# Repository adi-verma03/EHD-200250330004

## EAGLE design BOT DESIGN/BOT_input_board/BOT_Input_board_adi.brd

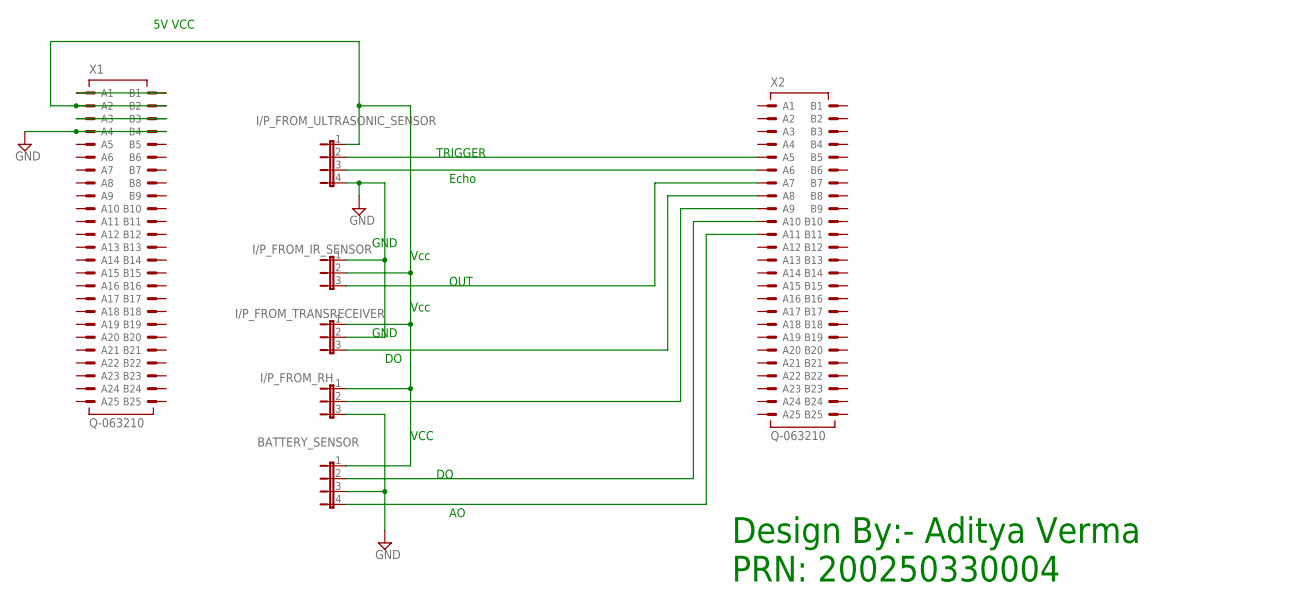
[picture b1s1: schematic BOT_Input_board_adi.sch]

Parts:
BATTERY_SENSOR: JP4E; JP4
I/P_FROM_IR_SENSOR: JP2E; JP2
I/P_FROM_RH: JP2E; JP2
I/P_FROM_TRANSRECEIVER: JP2E; JP2
I/P_FROM_ULTRASONIC_SENSOR: JP4E; JP4
X1, X2: Q-063210; 063210

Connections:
GND: BATTERY_SENSOR.3, I/P_FROM_IR_SENSOR.1, I/P_FROM_RH.3, I/P_FROM_TRANSRECEIVER.2, I/P_FROM_ULTRASONIC_SENSOR.4, X1.A4, X1.B4
unnamed: I/P_FROM_ULTRASONIC_SENSOR.3, X2.A6
unnamed: X1.A1, X1.B1
unnamed: BATTERY_SENSOR.1, I/P_FROM_IR_SENSOR.2, I/P_FROM_RH.1, I/P_FROM_TRANSRECEIVER.1, I/P_FROM_ULTRASONIC_SENSOR.1, X1.A2, X1.B2
unnamed: X1.A3, X1.B3
unnamed: I/P_FROM_ULTRASONIC_SENSOR.2, X2.A5
unnamed: I/P_FROM_IR_SENSOR.3, X2.A7
unnamed: I/P_FROM_TRANSRECEIVER.3, X2.A8
unnamed: I/P_FROM_RH.2, X2.A9
unnamed: BATTERY_SENSOR.2, X2.A10
unnamed: BATTERY_SENSOR.4, X2.A11

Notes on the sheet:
5V VCC
Vcc
GND
TRIGGER
Echo
OUT
VCC
Design By:- Aditya Verma PRN: 200250330004

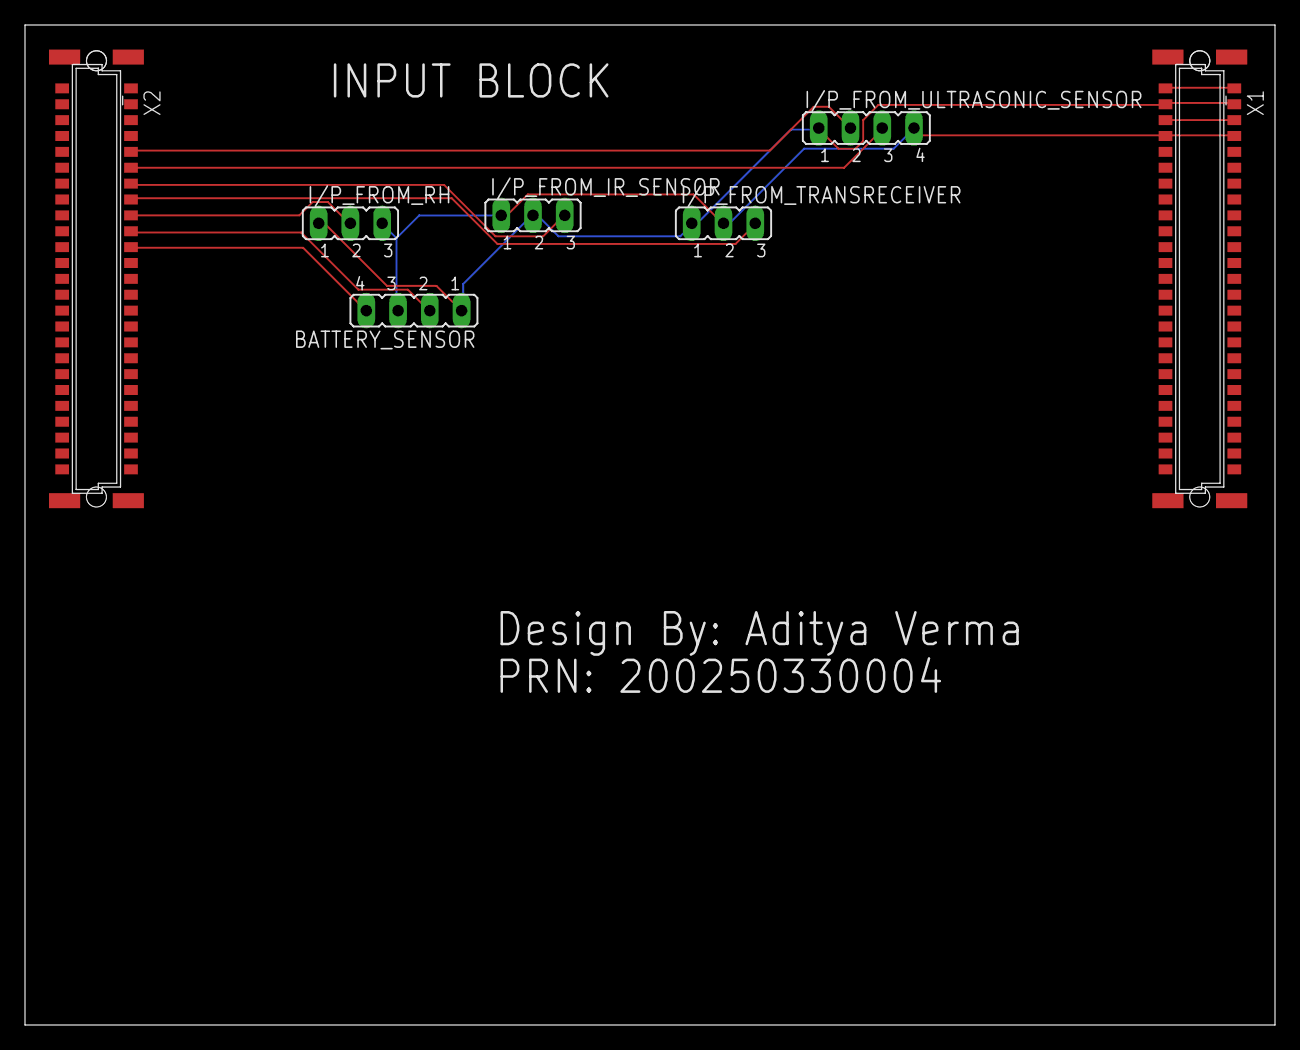
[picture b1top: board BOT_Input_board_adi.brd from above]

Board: 2 copper layers, 100.0 x 80.0 mm, 7 parts (0 on the bottom side), 11 nets.

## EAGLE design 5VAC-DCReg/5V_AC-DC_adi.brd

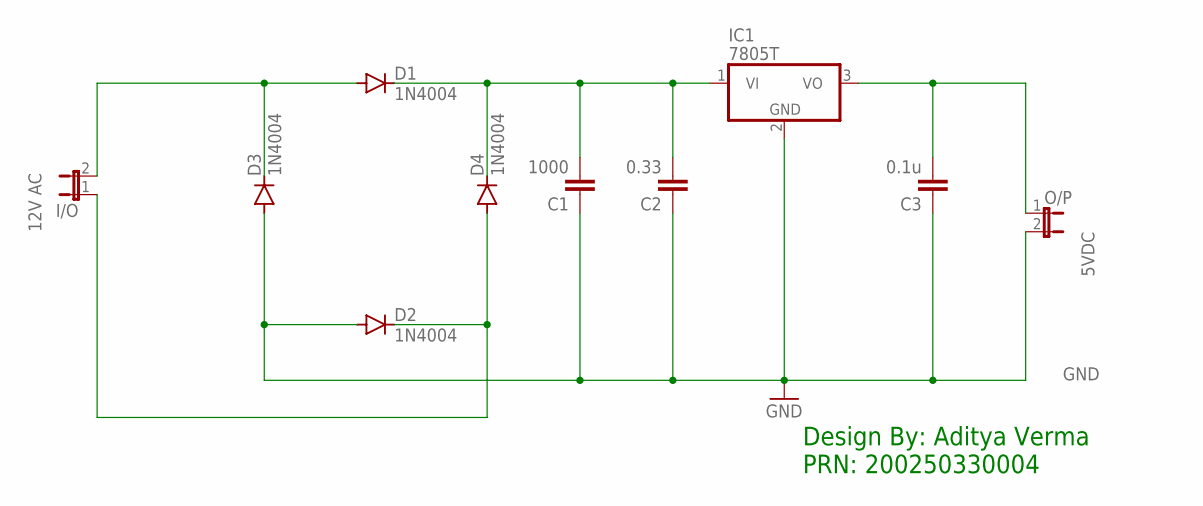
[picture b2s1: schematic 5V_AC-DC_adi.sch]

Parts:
C1: 1000; C2.5-3
C2: 0.33; C2.5-3
C3: 0.1u; C2.5-3
D1, D2, D3, D4: 1N4004; DO41-10
I/O: JP1E; JP1
IC1: 7805T; TO220H
O/P: JP1E; JP1

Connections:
GND: C1.1, C2.1, C3.1, D2.A, D3.A, IC1.2 (GND), O/P.2
unnamed: D1.A, D3.C, I/O.2
unnamed: D2.C, D4.A, I/O.1
unnamed: C1.2, C2.2, D1.C, D4.C, IC1.1 (VI)
unnamed: C3.2, IC1.3 (VO), O/P.1

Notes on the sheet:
Design By: Aditya Verma PRN: 200250330004

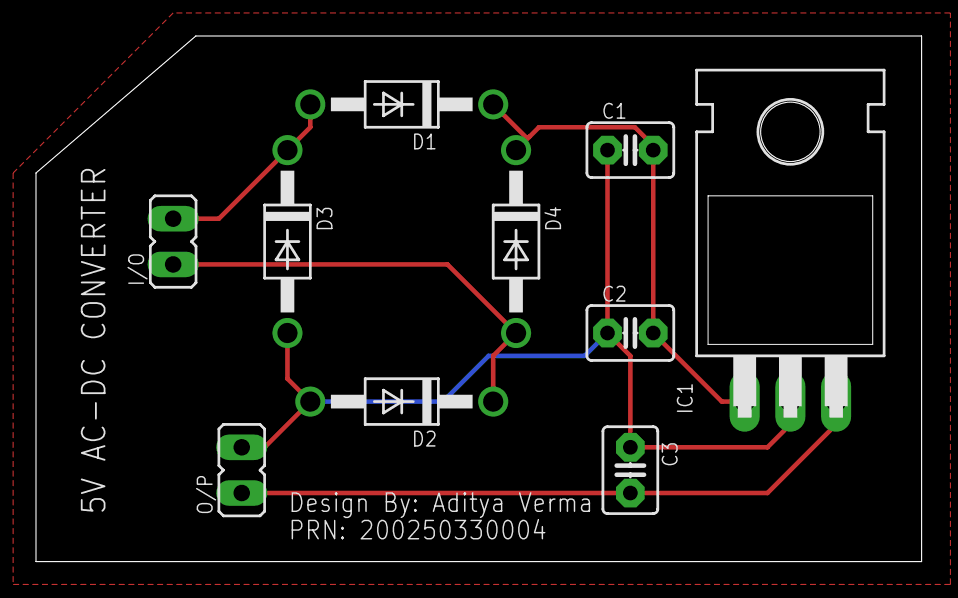
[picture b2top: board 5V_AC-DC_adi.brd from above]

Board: 2 copper layers, 49.2 x 29.2 mm, 10 parts (0 on the bottom side), 5 nets.

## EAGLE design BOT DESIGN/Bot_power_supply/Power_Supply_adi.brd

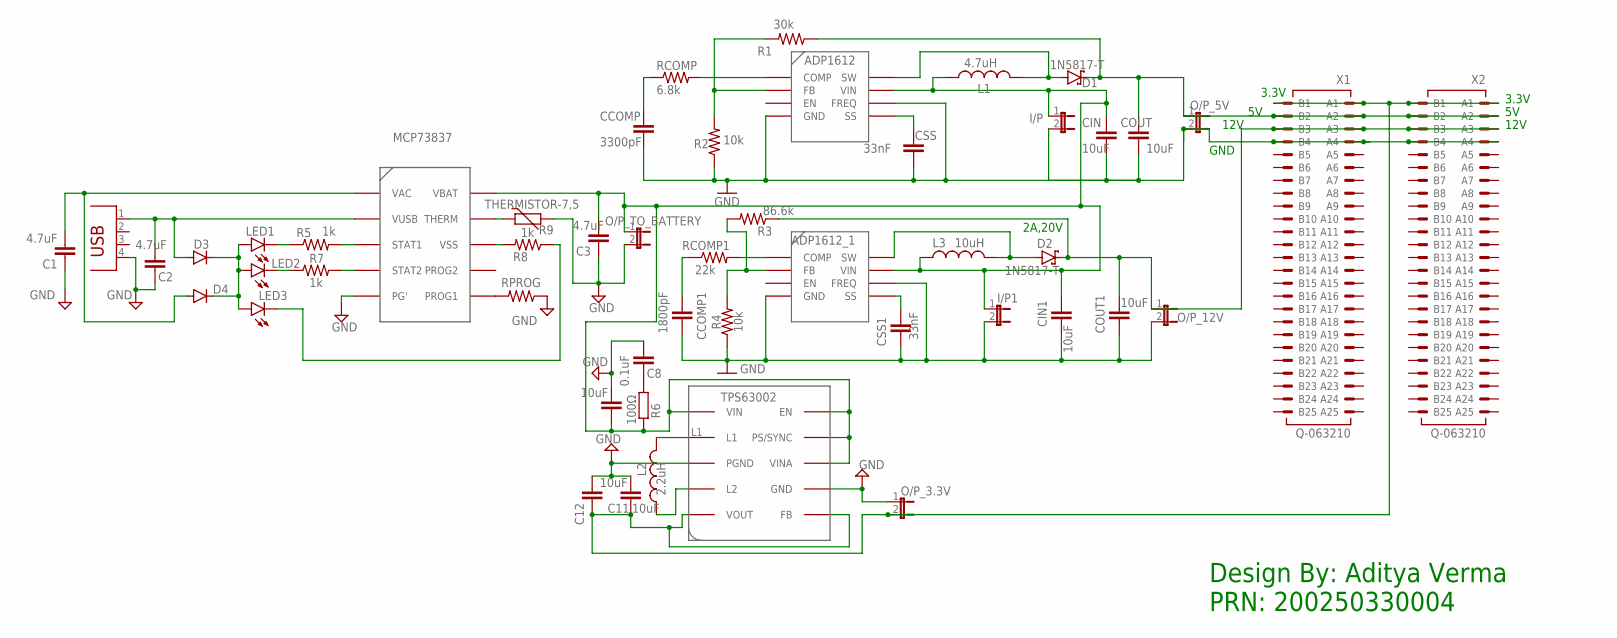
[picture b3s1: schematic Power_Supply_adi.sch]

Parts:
ADP1612, ADP1612_1: ADP1612_DEV; ADP1612_FOOT
C1, C2, C3: 4.7uF; C2.5-3
C8: 0.1uF; C2.5-2
C10, C11, C12: 10uF; C2.5-2
CCOMP: 3300pF; C2.5-3
CCOMP1: 1800pF; C2.5-3
CIN, CIN1: 10uF; C2.5-3
COUT, COUT1: 10uF; C2.5-3
CSS, CSS1: 33nF; C2.5-3
D1, D2: 1N5817-T; DO41-7.6
D3, D4: 1N4004; DO41-10
I/P, I/P1: JP1E; JP1
L1: 4.7uH; 0204/7
L2: 2.2uH; 0207/7
L3: 10uH; 0204/7
LED1, LED3: LED3MM
LED2: LEDLD260; LD260
MCP73837: MCP73837-DEV; MCP73837
O/P_3.3V, O/P_5V, O/P_12V: JP1E; JP1
O/P_TO_BATTERY: JP1E; JP1
R1: 30k; 0204V
R2, R4: 10k; 0204V
R3: 86.6k; 0204V
R5, R7, R8: 1k; 0204V
R6: 100Ω; 0207/10
R9: THERMISTOR-7,5; R-7,5
RCOMP: 6.8k; 0204V
RCOMP1: 22k; 0204V
RPROG: R-US_0204/2V; 0204V
TPS63002: TPS63002
USB: PN61729
X1, X2: Q-063210; 063210

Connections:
GND: ADP1612.FREQ, ADP1612.GND, ADP1612_1.FREQ, ADP1612_1.GND, C1.1, C2.1, C3.1, C8.2, C10.2, C11.2, C12.2, CCOMP.2, CCOMP1.2, CIN.2, CIN1.2, COUT.2, COUT1.2, CSS.2, CSS1.2, I/P.2, I/P1.2, MCP73837.PG', O/P_3.3V.1, O/P_5V.2, O/P_12V.2, O/P_TO_BATTERY.2, R2.1, R4.1, R9.2, RPROG.1, TPS63002.GND, TPS63002.PGND, USB.4, X1.A4, X1.B4, X2.A4, X2.B4
unnamed: ADP1612.COMP, RCOMP.2
unnamed: CCOMP.1, RCOMP.1
unnamed: COUT.1, D1.C, O/P_5V.1, R1.1, X1.A2, X1.B2, X2.A2, X2.B2
unnamed: ADP1612.FB, R1.2, R2.2
unnamed: L2.1, TPS63002.L1
unnamed: ADP1612.SS, CSS.1
unnamed: ADP1612.SW, D1.A, L1.2
unnamed: ADP1612_1.COMP, RCOMP1.2
unnamed: CCOMP1.1, RCOMP1.1
unnamed: COUT1.1, D2.C, O/P_12V.1, R3.1, X1.A3, X1.B3, X2.A3, X2.B3
unnamed: L2.2, TPS63002.L2
unnamed: ADP1612_1.FB, R3.2, R4.2
unnamed: ADP1612_1.SS, CSS1.1
unnamed: MCP73837.VSS, R8.2
unnamed: ADP1612_1.SW, D2.A, L3.2
unnamed: MCP73837.STAT1, R5.2
unnamed: MCP73837.STAT2, R7.2
unnamed: ADP1612.VIN, ADP1612_1.VIN, C3.2, C10.1, CIN.1, CIN1.1, I/P.1, I/P1.1, L1.1, L3.1, MCP73837.VBAT, O/P_TO_BATTERY.1, R6.1, TPS63002.EN, TPS63002.PS/SYNC, TPS63002.VIN, TPS63002.VINA
unnamed: C8.1, R6.2
unnamed: MCP73837.PROG1, RPROG.2
unnamed: MCP73837.THERM, R9.1
unnamed: C2.2, D3.A, MCP73837.VUSB, USB.1
unnamed: LED1.K (C), R5.1
unnamed: LED2.K (C), R7.1
unnamed: D3.C, D4.C, LED1.A, LED2.A, LED3.A
unnamed: C1.2, D4.A, MCP73837.VAC
unnamed: LED3.K (C), R8.1
unnamed: C11.1, C12.1, O/P_3.3V.2, TPS63002.FB, TPS63002.VOUT, X1.A1, X1.B1, X2.A1, X2.B1

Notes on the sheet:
2A,20V
3.3V
12V
GND
Design By: Aditya Verma PRN: 200250330004

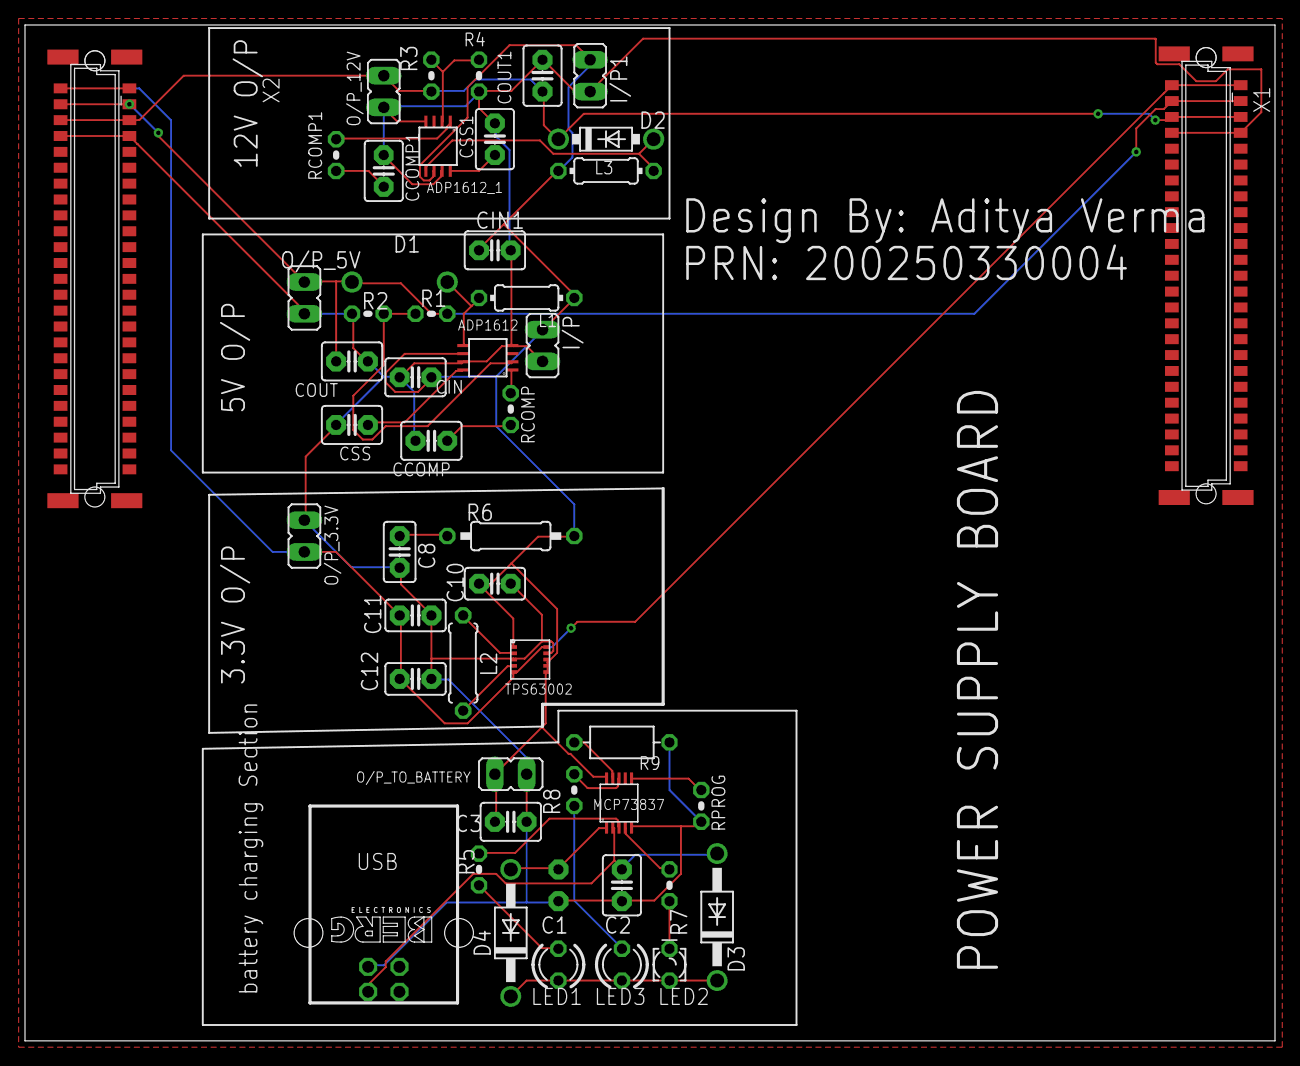
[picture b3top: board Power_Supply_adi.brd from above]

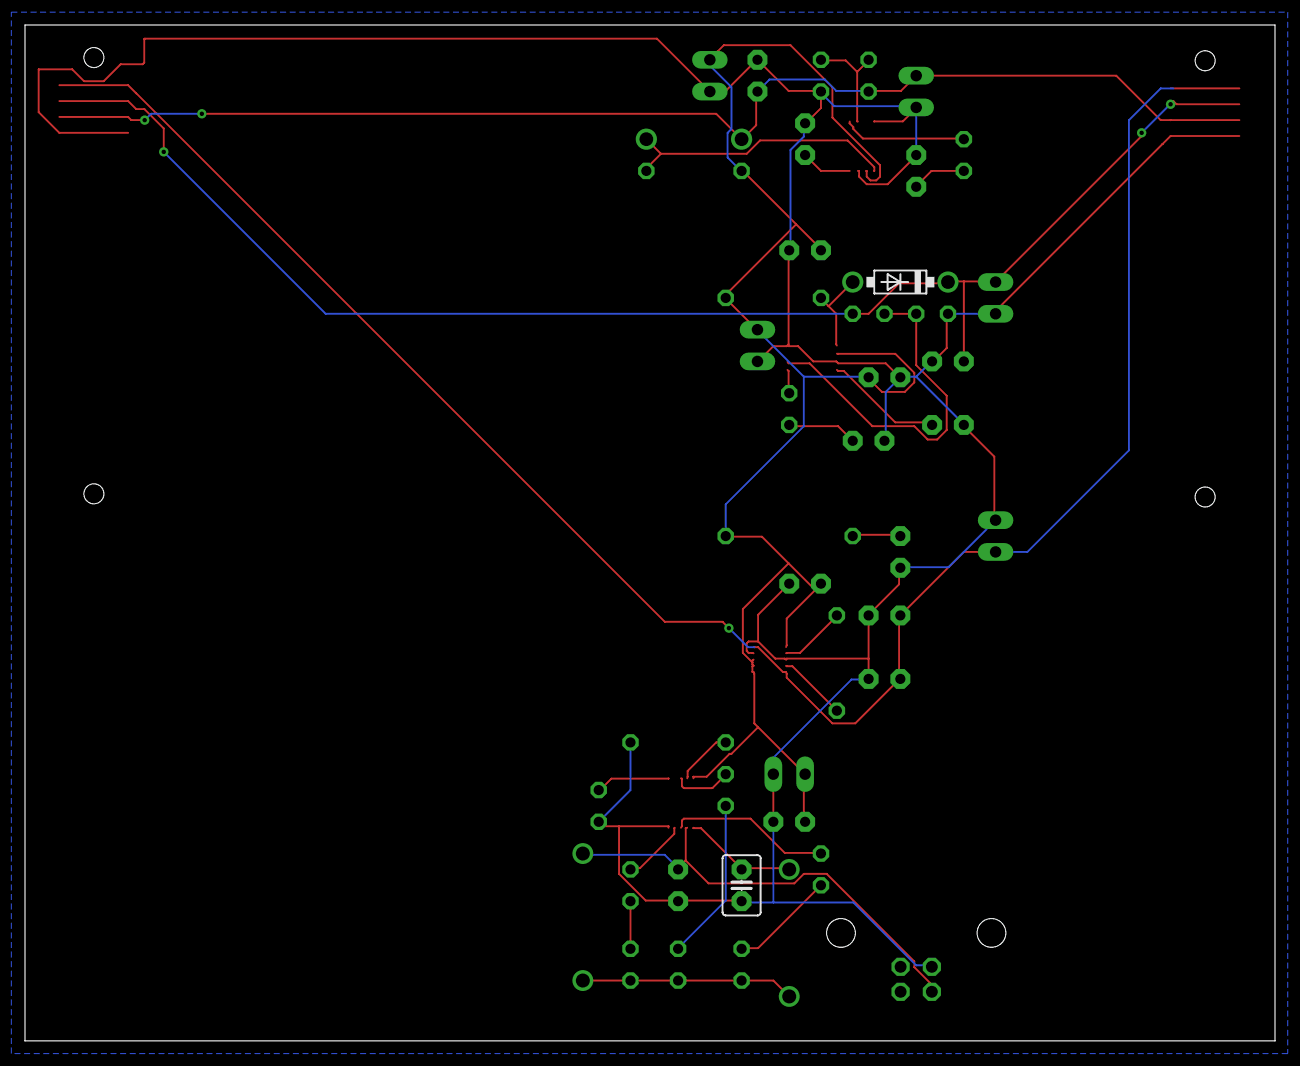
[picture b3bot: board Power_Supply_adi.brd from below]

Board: 2 copper layers, 100.0 x 81.3 mm, 50 parts (2 on the bottom side), 29 nets.

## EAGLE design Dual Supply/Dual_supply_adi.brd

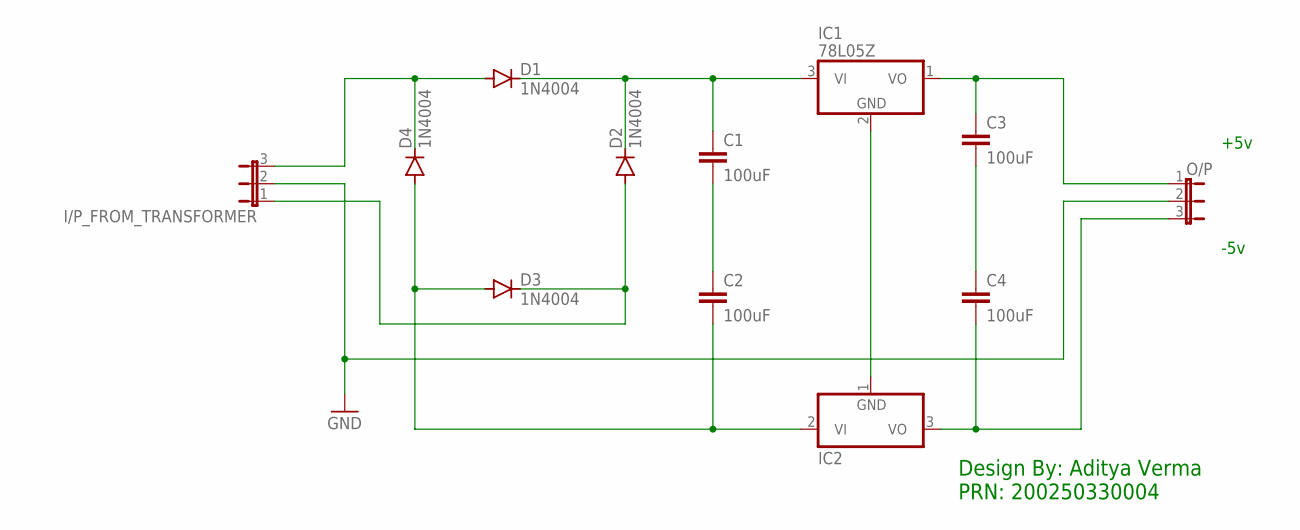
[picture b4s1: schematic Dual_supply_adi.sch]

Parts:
C1, C2, C3, C4: 100uF; C2.5-3
D1, D2, D3, D4: 1N4004; DO41-10
I/P_FROM_TRANSFORMER: JP2E; JP2
IC1: 78L05Z; TO92
IC2: 79L05Z; TO92
O/P: JP2E; JP2

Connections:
GND: I/P_FROM_TRANSFORMER.2, O/P.2
unnamed: C2.2, D3.A, D4.A, IC2.2 (VI)
unnamed: IC1.2 (GND), IC2.1 (GND)
unnamed: C4.2, IC2.3 (VO), O/P.3
unnamed: D1.A, D4.C, I/P_FROM_TRANSFORMER.3
unnamed: C1.1, D1.C, D2.C, IC1.3 (VI)
unnamed: D2.A, D3.C, I/P_FROM_TRANSFORMER.1
unnamed: C3.2, C4.1
unnamed: C1.2, C2.1
unnamed: C3.1, IC1.1 (VO), O/P.1

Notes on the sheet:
+5v
-5v
Design By: Aditya Verma PRN: 200250330004

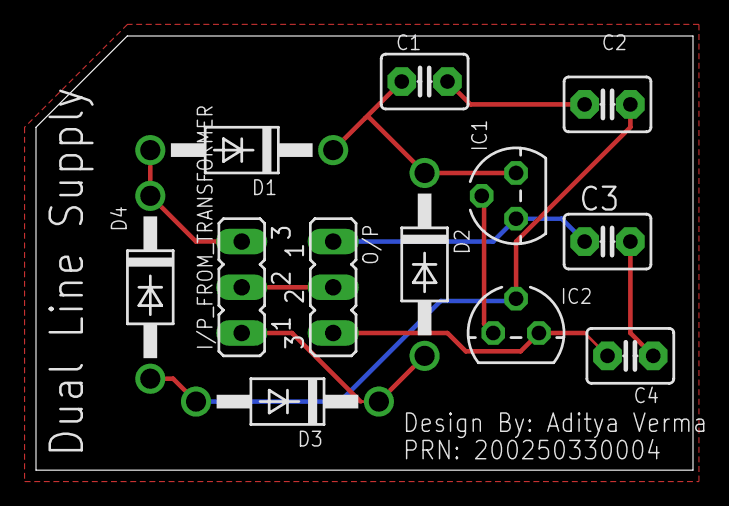
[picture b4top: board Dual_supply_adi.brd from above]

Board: 2 copper layers, 36.5 x 24.1 mm, 12 parts (0 on the bottom side), 10 nets.

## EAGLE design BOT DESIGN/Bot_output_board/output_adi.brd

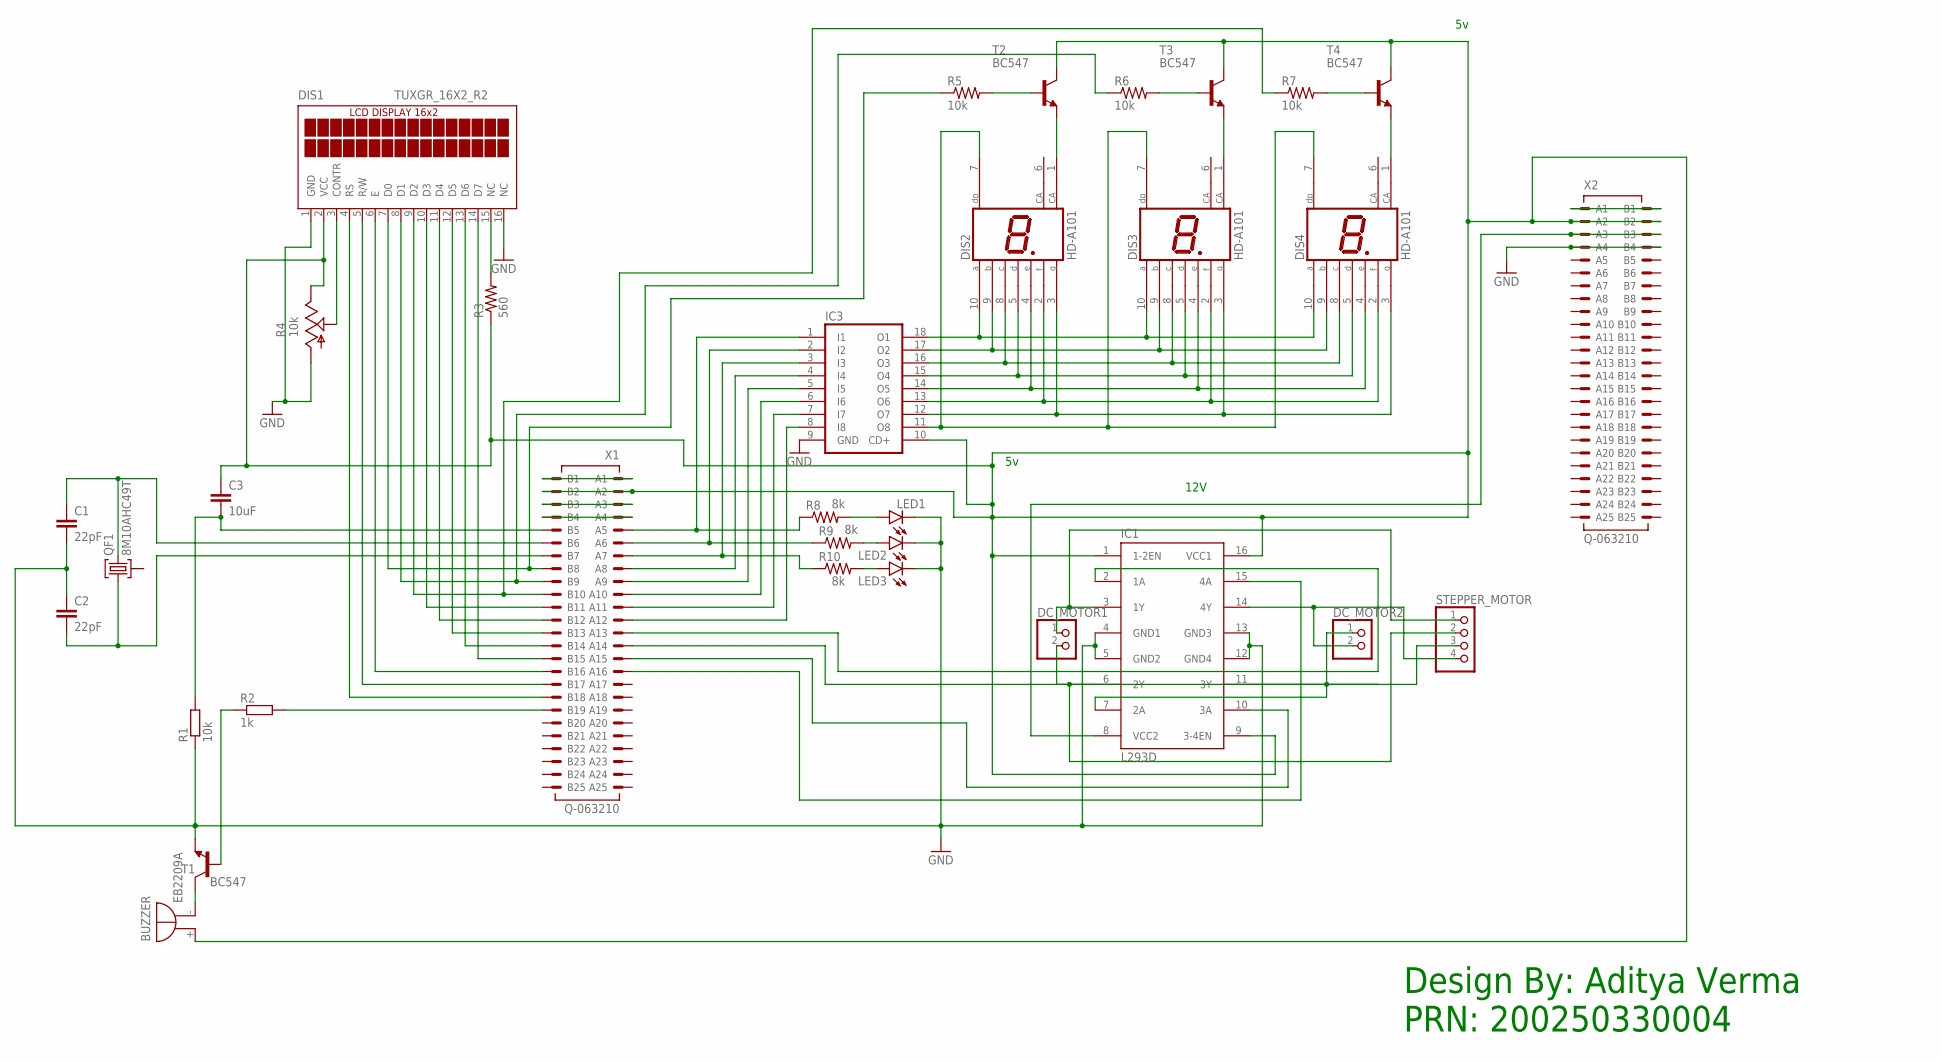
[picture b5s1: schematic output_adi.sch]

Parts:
BUZZER: EB2209A
C1, C2: 22pF; C2.5-3
C3: 10uF; C2.5-3
DC_MOTOR1, DC_MOTOR2: PINHD-1X2; 1X02
DIS1: TUXGR_16X2_R2
DIS2, DIS3, DIS4: HD-A101; HDSP-A
IC1: L293D; DIL16
IC3: ULN2803A; DIL18
LED1, LED2, LED3: LED5MM
QF1: 8M10AHC49T; HC49U
R1, R5, R6, R7: 10k; 0204V
R2: 1k; 0204V
R3: 560; 0204V
R4: 10k; CA6V
R8, R9, R10: 8k; 0204V
STEPPER_MOTOR: PINHD-1X4; 1X04
T1, T2, T3, T4: BC547; TO92
X1, X2: Q-063210; 063210

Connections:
GND: C1.2, C2.1, DIS1.1 (GND), DIS1.16 (NC), IC1.4 (GND1), IC1.5 (GND2), IC1.12 (GND4), IC1.13 (GND3), IC3.9 (GND), LED1.K (C), LED2.K (C), LED3.K (C), R1.1, R4.A, T1.1 (E), X2.A4, X2.B4
unnamed: DC_MOTOR1.1, IC1.3 (1Y), STEPPER_MOTOR.1
unnamed: DC_MOTOR1.2, IC1.6 (2Y), STEPPER_MOTOR.2
unnamed: DC_MOTOR2.2, IC1.14 (4Y), STEPPER_MOTOR.4
unnamed: DC_MOTOR2.1, IC1.7 (2A), IC1.11 (3Y), STEPPER_MOTOR.3
unnamed: C3.2, R1.2, X1.B5
unnamed: C1.1, QF1.3, X1.B6
unnamed: IC1.2 (1A), X1.A13
unnamed: IC1.10 (3A), X1.A15
unnamed: IC1.15 (4A), X1.A16
unnamed: R2.2, X1.B19
unnamed: C2.2, QF1.1, X1.B7
unnamed: R2.1, T1.2 (B)
unnamed: BUZZER.-, T1.3 (C)
unnamed: DIS1.14 (D7), X1.B15
unnamed: DIS1.13 (D6), X1.B14
unnamed: X2.A1, X2.B1
unnamed: DIS1.11 (D4), X1.B12
unnamed: DIS1.10 (D3), X1.B11
unnamed: DIS1.9 (D2), R7.1, X1.B10
unnamed: DIS1.8 (D1), R6.1, X1.B9
unnamed: DIS1.12 (D5), X1.B13
unnamed: DIS1.15 (NC), R3.2
unnamed: DIS1.6 (E), X1.B16
unnamed: DIS1.5 (R/W), X1.B17
unnamed: DIS1.4 (RS), X1.B18
unnamed: DIS1.3 (CONTR), R4.S
unnamed: IC3.8 (I8), X1.A12
unnamed: IC3.7 (I7), X1.A11
unnamed: IC3.6 (I6), X1.A10
unnamed: IC3.5 (I5), X1.A9
unnamed: IC3.4 (I4), X1.A8
unnamed: IC3.2 (I2), R9.1, X1.A6
unnamed: IC3.1 (I1), R8.1, X1.A5
unnamed: DIS2.10 (A), DIS3.10 (A), DIS4.10 (A), IC3.18 (O1)
unnamed: DIS2.9 (B), DIS3.9 (B), DIS4.9 (B), IC3.17 (O2)
unnamed: DIS2.8 (C), DIS3.8 (C), DIS4.8 (C), IC3.16 (O3)
unnamed: DIS2.5 (D), DIS3.5 (D), DIS4.5 (D), IC3.15 (O4)
unnamed: DIS2.4 (E), DIS3.4 (E), DIS4.4 (E), IC3.14 (O5)
unnamed: DIS2.2 (F), DIS3.2 (F), DIS4.2 (F), IC3.13 (O6)
unnamed: DIS2.3 (G), DIS3.3 (G), DIS4.3 (G), IC3.12 (O7)
unnamed: DIS2.1 (CA), T2.1 (E)
unnamed: DIS2.7 (DP), DIS3.7 (DP), DIS4.7 (DP), IC3.11 (O8)
unnamed: DIS3.1 (CA), T3.1 (E)
unnamed: DIS4.1 (CA), T4.1 (E)
unnamed: R5.2, T2.2 (B)
unnamed: R6.2, T3.2 (B)
unnamed: R7.2, T4.2 (B)
unnamed: LED1.A, R8.2
unnamed: LED2.A, R9.2
unnamed: LED3.A, R10.2
unnamed: IC1.8 (VCC2), X2.A3, X2.B3
unnamed: DIS1.7 (D0), R5.1, X1.B8
unnamed: X1.A1, X1.B1
unnamed: BUZZER.+, C3.1, DIS1.2 (VCC), IC1.1 (1-2EN), IC1.9 (3-4EN), IC1.16 (VCC1), IC3.10 (CD+), R3.1, R4.E, T2.3 (C), T3.3 (C), T4.3 (C), X1.A2, X1.B2, X2.A2, X2.B2
unnamed: X1.A3, X1.B3
unnamed: X1.A4, X1.B4
unnamed: IC3.3 (I3), R10.1, X1.A7

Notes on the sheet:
12V
Design By: Aditya Verma PRN: 200250330004

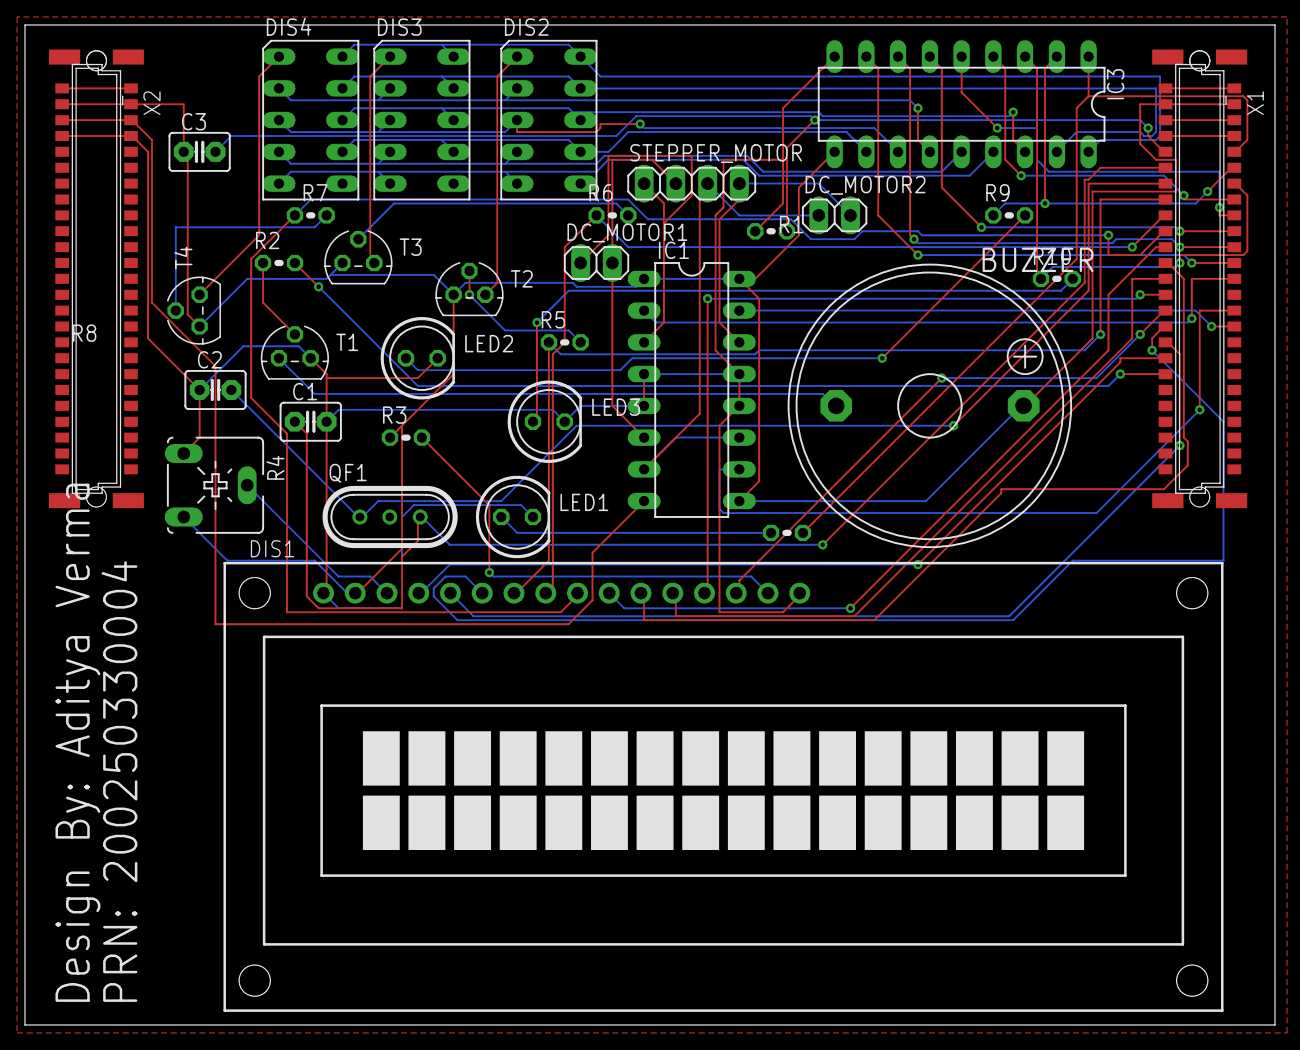
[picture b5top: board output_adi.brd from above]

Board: 2 copper layers, 100.0 x 80.0 mm, 33 parts (0 on the bottom side), 58 nets.

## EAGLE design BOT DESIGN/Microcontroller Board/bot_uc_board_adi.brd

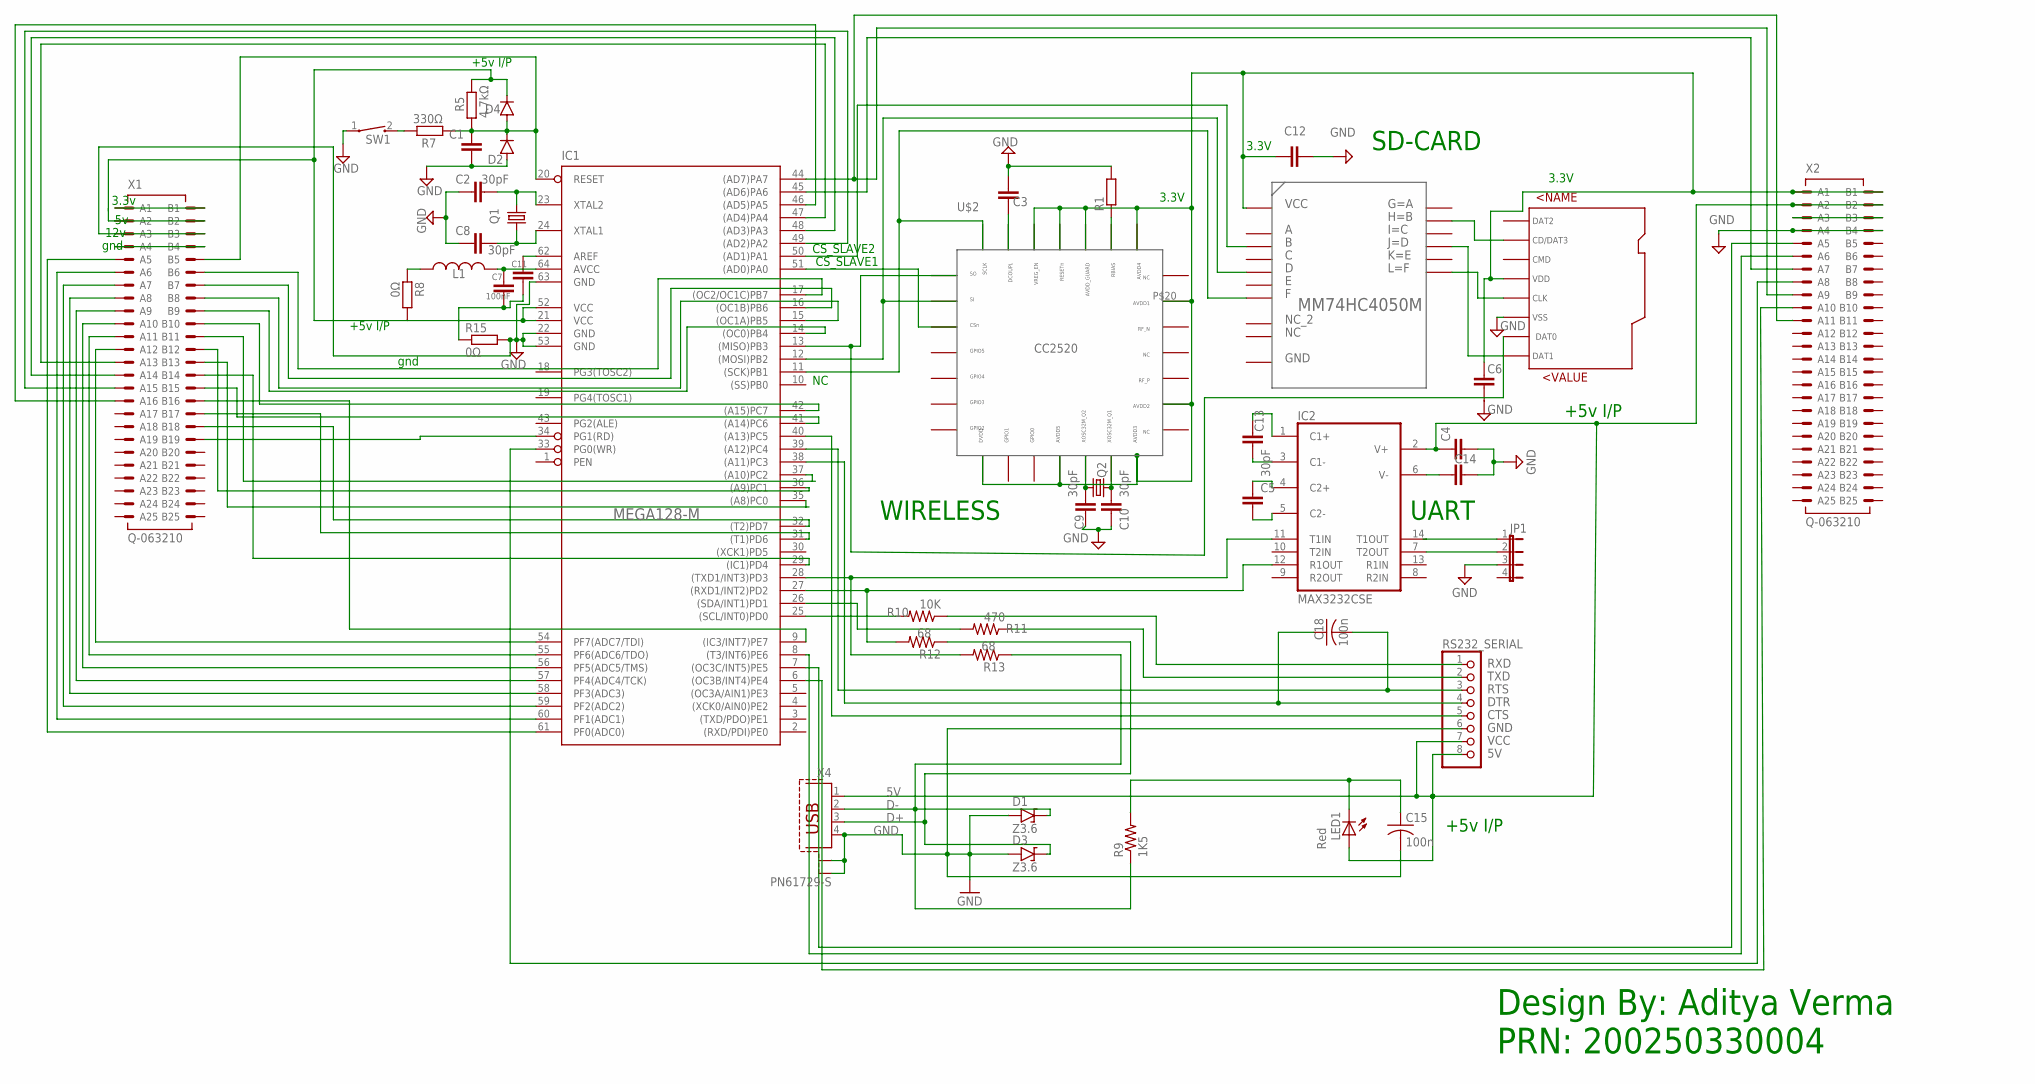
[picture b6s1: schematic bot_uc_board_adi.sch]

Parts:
C1, C3, C4, C5, C7, C12, C14: C-EU025-024X044; C025-024X044
C2, C6, C8, C9, C10, C13: 30pF; C025-024X044
C11: 100nF; C025-024X044
C15, C18: 100n; C050-024X044
D1, D3: Z3.6; DO35-3
D2, D4: 1N4004; DO41-10
IC1: MEGA128-M; MLF64
IC2: MAX3232CSE; SO16
JP1: JP4E; JP4
L1: L-US0204/5; 0204/5
LED1: Red; LED3MM
Q1, Q2: CRYSTALHC49U-V; HC49U-V
R1: R-EU_0204/2V; 0204V
R5: 4.7kΩ; 0204V
R7: 330Ω; 0204V
R8, R15: 0Ω; 0204V
R9: 1K5; 0207/7
R10: 10K; 0207/7
R11: 470; 0207/7
R12, R13: 68; 0207/7
RS232_SERIAL: PINHD-1X8/90; 1X08/90
SW1: CT10-XXXX-A2
U$1: 74HC4050; 74HC405
U$2: CC2520; CC2520_FOOT
U$3: SDCARD; SDCARD_FOOT
X1, X2: Q-063210; 063210
X4: PN61729-S

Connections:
3.3V_VCC: D4.C, IC1.21 (VCC), IC1.52 (VCC), IC2.16 (VCC), R5.2, R8.2
D+: D3.C, R12.1, X4.3
D-: D1.C, R9.1, R13.1, X4.2
GND: C1.1, C2.1, C3.1, C4.2, C6.1, C8.1, C9.1, C10.1, C12.2, C14.2, C15.2, D1.A, D2.A, D3.A, IC1.22 (GND), IC1.53 (GND), IC1.63 (GND), IC2.15 (GND), JP1.3, R1.2, R15.2, RS232_SERIAL.6, SW1.1, U$3.P$6 (VSS), X1.A3, X1.B3, X2.A4, X2.B4, X4.4, X4.S1, X4.S2
unnamed: D2.C, D4.A, IC1.20 (RESET), R5.1, R7.1, X1.B5
unnamed: IC1.12 ((MOSI)PB2), U$1.P$9 (D), U$2.P$2
unnamed: C7.1, IC1.64 (AVCC), L1.1
unnamed: L1.2, R8.1
unnamed: IC1.51 ((AD0)PA0), U$2.P$3
unnamed: R7.2, SW1.2
unnamed: IC1.13 ((MISO)PB3), U$2.P$1, U$3.P$7 (DAT0)
unnamed: C2.2, IC1.23 (XTAL2), Q1.2
unnamed: C8.2, IC1.24 (XTAL1), Q1.1
unnamed: C9.2, Q2.2, U$2.P$12
unnamed: C10.2, Q2.1, U$2.P$13
unnamed: IC1.11 ((SCK)PB1), U$1.P$14 (F), U$2.P$28
unnamed: C11.2, IC1.62 (AREF)
unnamed: C7.2, C11.1, R15.1
unnamed: R1.1, U$2.P$23
unnamed: C3.2, U$2.P$27
unnamed: U$1.P$4 (H), U$3.P$2 (CD/DAT3)
unnamed: C6.2, C12.1, U$1.P$1 (VCC), U$2.P$8, U$2.P$11, U$2.P$14, U$2.P$16, U$2.P$20, U$2.P$22, U$2.P$24, U$2.P$25, U$2.P$26, U$3.P$4 (VDD), X2.A1, X2.B1
unnamed: U$1.P$10 (J), U$3.P$8 (DAT1)
unnamed: U$1.P$15 (L), U$3.P$5 (CLK)
unnamed: IC1.50 ((AD1)PA1), U$1.P$5 (B)
unnamed: X1.A2, X1.B2
unnamed: C4.1, IC2.2 (V+), LED1.A, RS232_SERIAL.7, RS232_SERIAL.8, X2.A2, X2.B2, X4.1
unnamed: C14.1, IC2.6 (V-)
unnamed: C5.1, IC2.4 (C2+)
unnamed: C13.1, IC2.1 (C1+)
unnamed: C5.2, IC2.5 (C2-)
unnamed: C13.2, IC2.3 (C1-)
unnamed: IC2.14 (T1OUT), JP1.1
unnamed: IC2.7 (T2OUT), JP1.2
unnamed: C15.1, LED1.K (C), R9.2
unnamed: IC1.61 (PF0(ADC0)), X1.A5
unnamed: IC1.60 (PF1(ADC1)), X1.A6
unnamed: C18.1, IC1.38 ((A11)PC3), RS232_SERIAL.4
unnamed: C18.2, IC1.39 ((A12)PC4), RS232_SERIAL.3
unnamed: IC1.40 ((A13)PC5), RS232_SERIAL.5
unnamed: IC1.25 ((SCL/INT0)PD0), R10.2
unnamed: IC1.26 ((SDA/INT1)PD1), R11.2
unnamed: IC1.27 ((RXD1/INT2)PD2), IC2.12 (R1OUT), R12.2
unnamed: IC1.28 ((TXD1/INT3)PD3), IC2.11 (T1IN), R13.2
unnamed: IC1.59 (PF2(ADC2)), X1.A7
unnamed: IC1.58 (PF3(ADC3)), X1.A8
unnamed: IC1.57 (PF4(ADC4/TCK)), X1.A9
unnamed: IC1.56 (PF5(ADC5/TMS)), X1.A10
unnamed: IC1.55 (PF6(ADC6/TDO)), X1.A11
unnamed: IC1.54 (PF7(ADC7/TDI)), X1.A12
unnamed: IC1.47 ((AD4)PA4), X1.A13
unnamed: IC1.48 ((AD3)PA3), X1.A14
unnamed: IC1.49 ((AD2)PA2), X1.A15
unnamed: IC1.46 ((AD5)PA5), X1.A16
unnamed: X1.A1, X1.B1
unnamed: X1.A4, X1.B4
unnamed: IC1.31 ((T1)PD6), X1.B17
unnamed: IC1.32 ((T2)PD7), X1.B18
unnamed: IC1.34 (PG1(RD)), X1.B19
unnamed: IC1.9 ((IC3/INT7)PE7), X1.B16
unnamed: IC1.17 ((OC2/OC1C)PB7), X1.B6
unnamed: IC1.16 ((OC1B)PB6), X1.B7
unnamed: IC1.15 ((OC1A)PB5), X1.B8
unnamed: IC1.14 ((OC0)PB4), X1.B9
unnamed: IC1.42 ((A15)PC7), X1.B10
unnamed: IC1.41 ((A14)PC6), X1.B15
unnamed: IC1.37 ((A10)PC2), X1.B11
unnamed: IC1.36 ((A9)PC1), X1.B12
unnamed: IC1.35 ((A8)PC0), X1.B13
unnamed: IC1.29 ((IC1)PD4), X1.B14
unnamed: X2.A3, X2.B3
unnamed: IC1.7 ((OC3C/INT5)PE5), X2.A5
unnamed: IC1.8 ((T3/INT6)PE6), X2.A6
unnamed: IC1.45 ((AD6)PA6), X2.A7
unnamed: IC1.33 (PG0(WR)), X2.A8
unnamed: IC1.44 ((AD7)PA7), X2.A9, X2.A11
unnamed: IC1.6 ((OC3B/INT4)PE4), X2.A10
RXD: R10.1, RS232_SERIAL.1
TXD: R11.1, RS232_SERIAL.2

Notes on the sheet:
CS_SLAVE1
3.3V
CS_SLAVE2
+5v I/P
UART
WIRELESS
SD-CARD
RXD
TXD
RTS
DTR
CTS
GND
VCC
gnd
3.3v
12v
Design By: Aditya Verma PRN: 200250330004

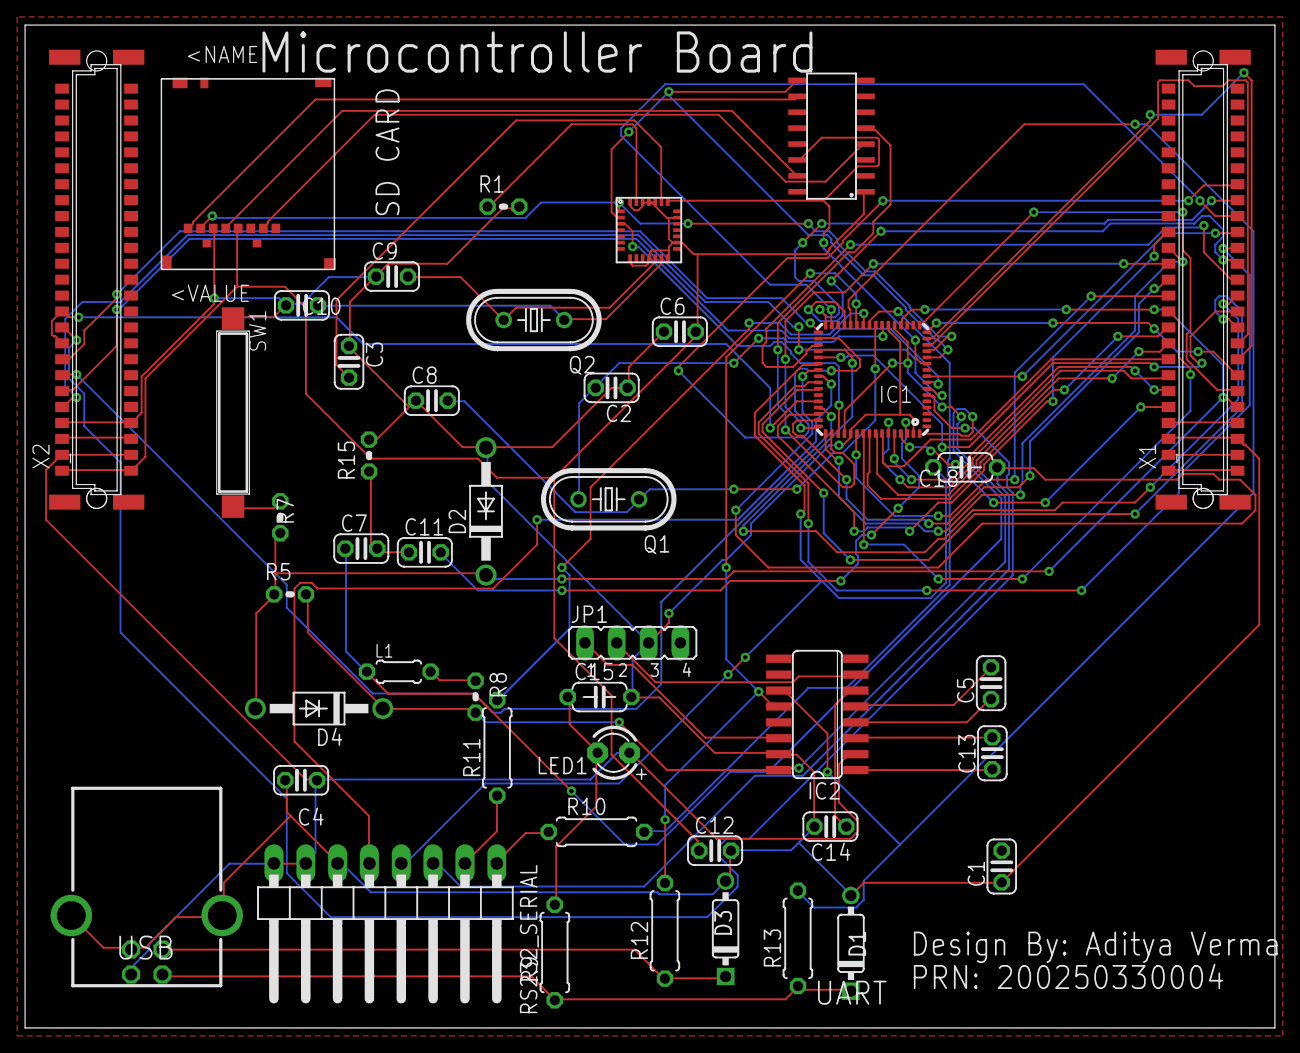
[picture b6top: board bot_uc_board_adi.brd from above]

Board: 2 copper layers, 99.7 x 80.0 mm, 45 parts (0 on the bottom side), 79 nets.
